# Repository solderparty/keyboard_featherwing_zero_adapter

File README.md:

# Raspberry Pi Zero Adapter for the Keyboard FeatherWing

This adapter was designed specifically to allow driving the Keyboard FeatherWing with a Raspberry Pi Zero board.

The SW support for the adapter is very limited right now, see https://github.com/solderparty/keyboard_featherwing_sw/wiki/RPi-Zero-Adapter to learn more about the progress.

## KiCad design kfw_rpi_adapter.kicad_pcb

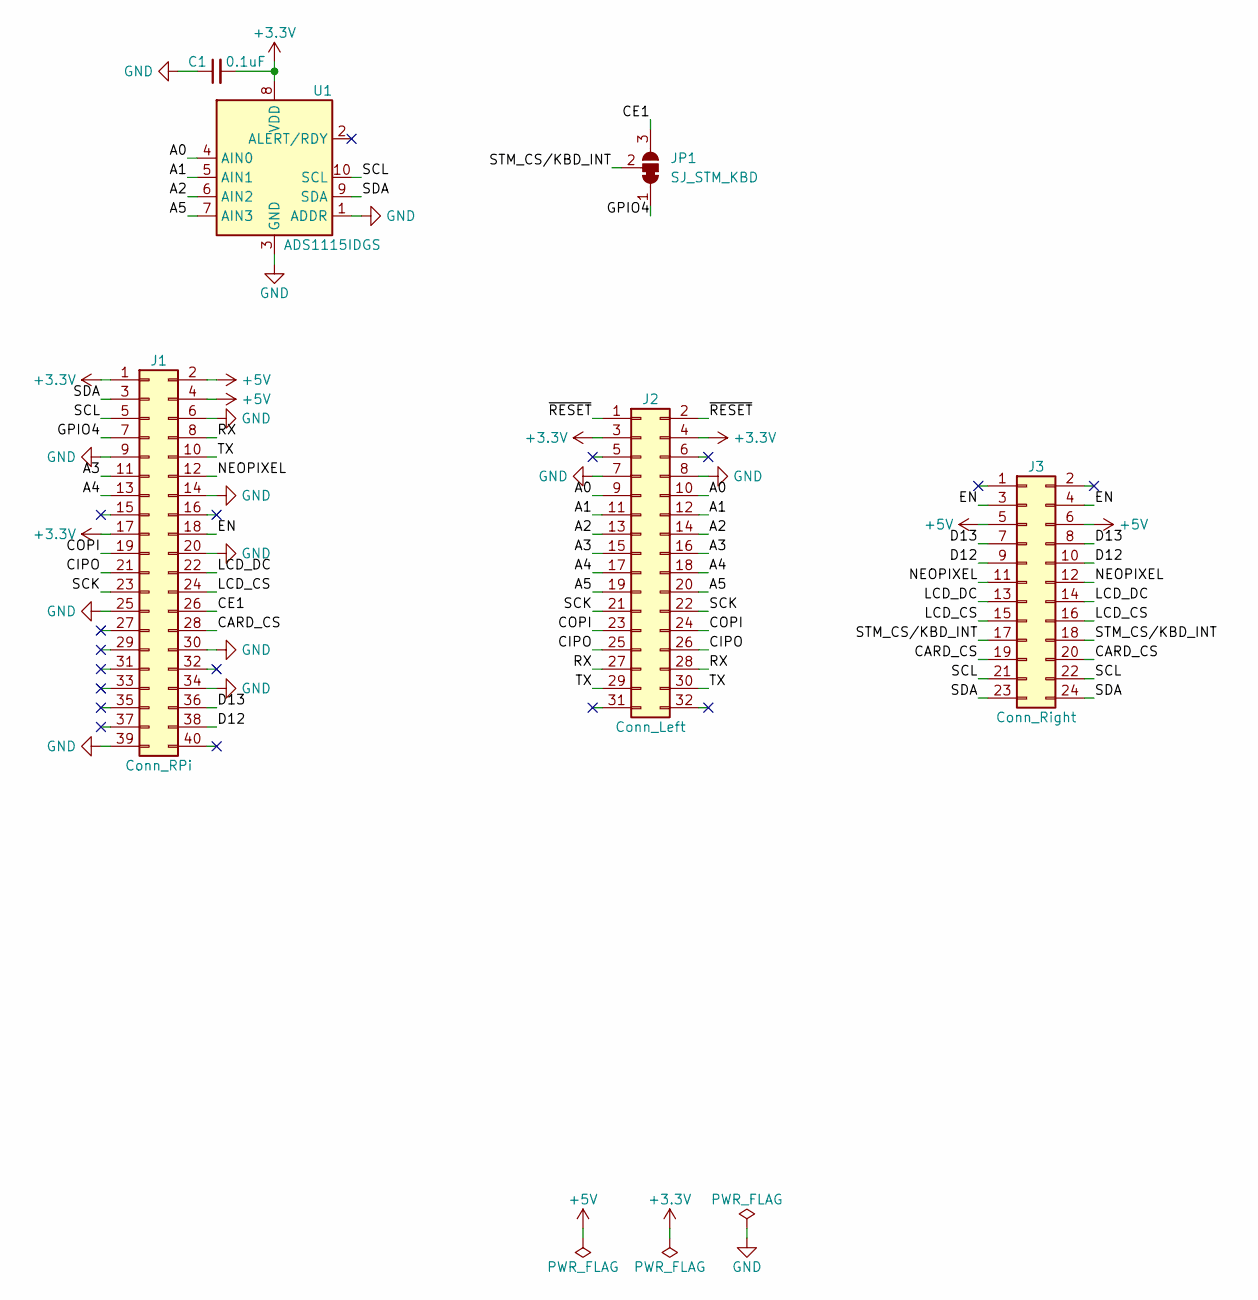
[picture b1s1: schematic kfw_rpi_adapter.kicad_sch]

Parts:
C1: 0.1uF; C_0603_1608Metric
J1: Conn_RPi; PinHeader_2x20_P2.54mm_Vertical
J2: Conn_Left; PinHeader_2x16_P2.54mm_Vertical
J3: Conn_Right; PinHeader_2x12_P2.54mm_Vertical
JP1: SJ_STM_KBD; SolderJumper-3_P1.3mm_Bridged12_RoundedPad1.0x1.5mm_NumberL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
U1: ADS1115IDGS; TSSOP-10_3x3mm_P0.5mm

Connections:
+3V3: C1.2, J1.1, J1.17, J2.3, J2.4, U1.8 (VDD)
+5V: J1.2, J1.4, J3.5, J3.6
/A0: J2.9, J2.10, U1.4 (AIN0)
/A1: J2.11, J2.12, U1.5 (AIN1)
/A2: J2.13, J2.14, U1.6 (AIN2)
/A3: J1.11, J2.15, J2.16
/A4: J1.13, J2.17, J2.18
/A5: J2.19, J2.20, U1.7 (AIN3)
/CARD_CS: J1.28, J3.19, J3.20
/CE1: J1.26, JP1.3 (B)
/CIPO: J1.21, J2.25, J2.26
/COPI: J1.19, J2.23, J2.24
/D12: J1.38, J3.9, J3.10
/D13: J1.36, J3.7, J3.8
/EN: J1.18, J3.3, J3.4
/GPIO4: J1.7, JP1.1 (A)
/LCD_CS: J1.24, J3.15, J3.16
/LCD_DC: J1.22, J3.13, J3.14
/NEOPIXEL: J1.12, J3.11, J3.12
/RX: J1.8, J2.27, J2.28
/SCK: J1.23, J2.21, J2.22
/SCL: J1.5, J3.21, J3.22, U1.10 (SCL)
/SDA: J1.3, J3.23, J3.24, U1.9 (SDA)
/STM_CS/KBD_INT: J3.17, J3.18, JP1.2 (C)
/TX: J1.10, J2.29, J2.30
/~RESET~: J2.1, J2.2
GND: C1.1, J1.6, J1.9, J1.14, J1.20, J1.25, J1.30, J1.34, J1.39, J2.7, J2.8, U1.1 (ADDR), U1.3 (GND)

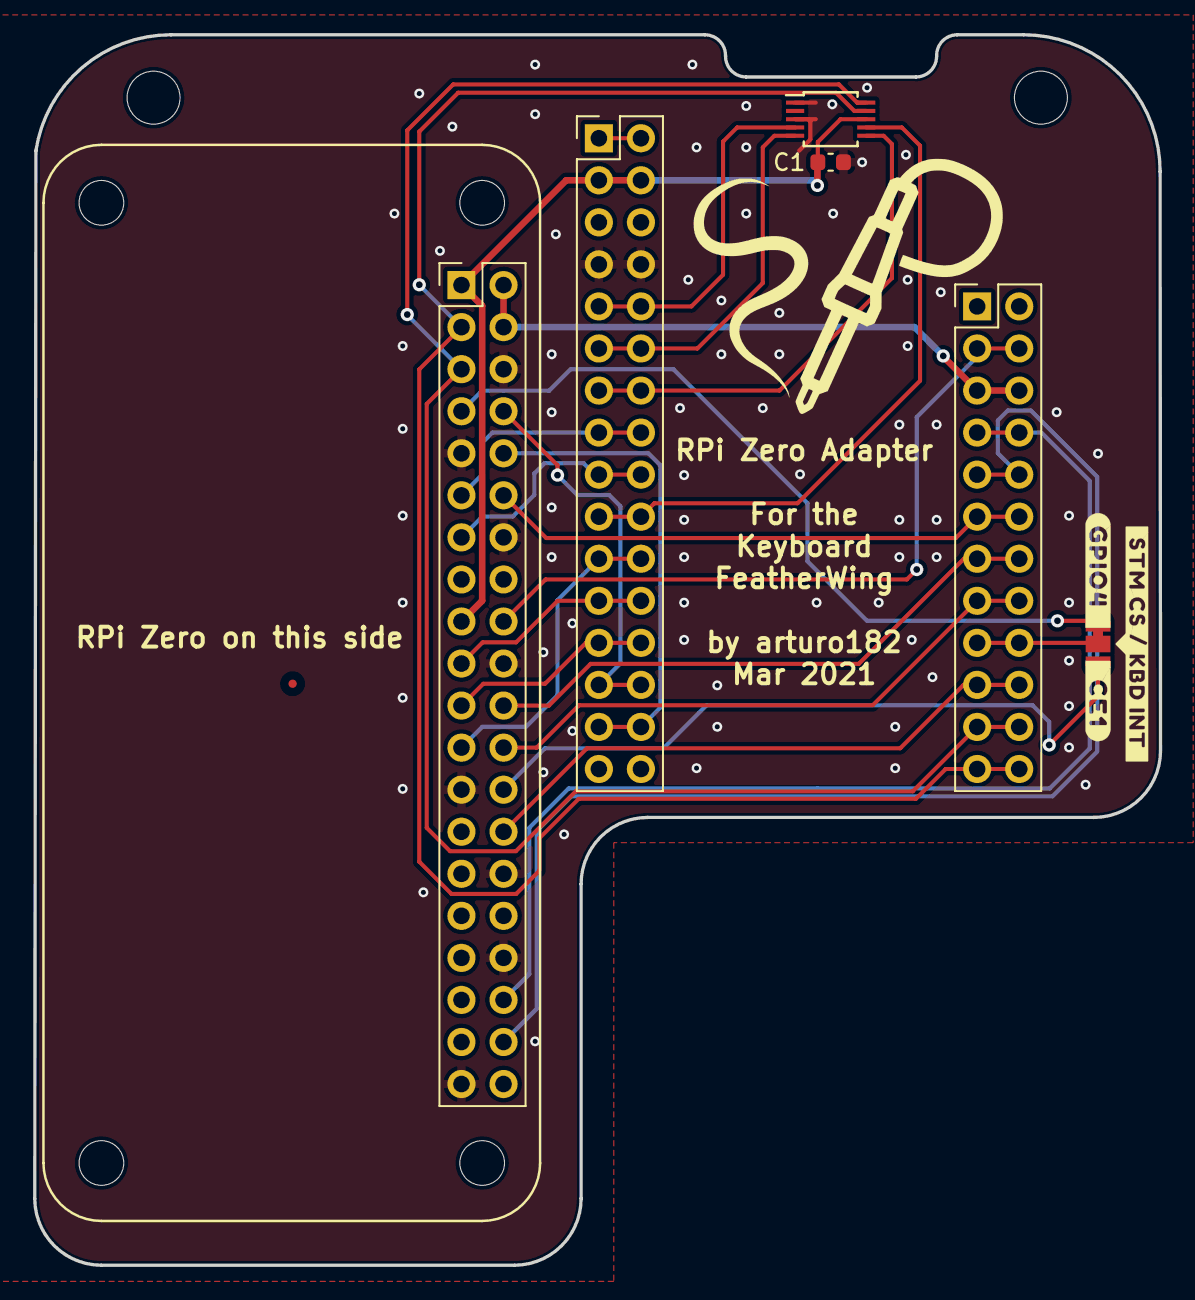
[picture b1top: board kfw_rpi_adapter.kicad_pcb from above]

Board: 2 copper layers, 68.0 x 74.3 mm, 6 parts (0 on the bottom side), 27 nets.

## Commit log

2021-07-21 Initial import
